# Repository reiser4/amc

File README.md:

# amc

Software utilizzato su Windows:

 Python 3.5.0
 https://www.python.org/ftp/python/3.5.0/python-3.5.0-amd64-webinstall.exe

 PyQt5 5.5
 http://sourceforge.net/projects/pyqt/files/PyQt5/PyQt-5.5/PyQt5-5.5-gpl-Py3.4-Qt5.5.0-x64.exe

 py2exe 0.9.2.0
 https://pypi.python.org/packages/any/p/py2exe/py2exe-0.9.2.0.win-amd64.exe#md5=05d90513c993b2f3ae0f7f21d69a6898

Per compilare per windows:

 python setup.py py2exe --includes sip

# funzionamento

il software AMC gira su beaglebone black. E` costituito da diversi componenti che interagiscono tra loro solamente tramite lettura e scrittura (atomica) di files in /tmp.

/tmp/band.txt
	contiene la banda in uso. puo` essere: 160, 80, 60, 40, 30, 20, 17, 15, 12, 10, 6

/tmp/relay.txt
	descrive i rele` attivi con la combinazione attuale di preset.
	esempio: 100000000000000000000000
	nella nostra implementazione usiamo i primi otto bits

/tmp/presetA.txt e /tmp/presetB.txt
	descrivono la combinazione da tastiera scelta dall'utente
	la pressione dei tasti provoca la variazione della combinazione
	esempio:
		TX: 01100000
		RX: 10010000

/tmp/presetTXTA.txt e /tmp/presetTXTB.txt
	contiene la lista testuale di preset attivi (per essere stampato sul display)
	senza spazi, separati da virgola, poi punto e virgola tra Rx e Tx
	esempio:
		Europa,Asia,America;Asia

/tmp/tx.txt
	contiene la lista di radio che stanno trasmettendo in quel momento
	esempio:
		A
		oppure
		B
		oppure 
		(file vuoto)

/root/amc/config.json
	contiene la configurazione con cui vengono determinate le varie combinazioni di relay da accendere.
	vedi file di esempio

# componenti software

MAIN:
	si occupa di prendere le decisioni riguardo i preset e relay da attivare.
	LEGGE: /root/amc/config.json /tmp/tx.txt /tmp/presetA.txt /tmp/presetB.txt /tmp/band.txt
	SCRIVE: /tmp/relay.txt /tmp/presetTXTA.txt /tmp/presetTXTB.txt

IOLOOP:
	ascolta il GPIO hardware per determinare la banda e la radio trasmittente.
	SCRIVE: /tmp/band.txt /tmp/tx.txt

DISPLAY:
	si occupa di mantenere il display aggiornato con lo stato attuale.
	LEGGE: /tmp/tx.txt /tmp/band.txt /tmp/presetTXTA.txt /tmp/presetTXTB.txt

KEYBOARD:
	rimane in ascolto di input da tastiera e fa i toggle dei bits dei preset
	LEGGE: /tmp/presetA.txt /tmp/presetB.txt
	SCRIVE: /tmp/presetA.txt /tmp/presetB.txt

SERIAL:
	svolge due funzioni: riporta periodicamente sulla seriale lo stato attuale per poter essere visualizzato sul pc,
	ed interagisce col pc per inviare e ricevere la configurazione.
	LEGGE: /tmp/presetA.txt /tmp/presetB.txt /tmp/tx.txt /tmp/band.txt /tmp/presetTXTA.txt /tmp/presetTXTB.txt /root/amc/config.json
	SCRIVE: /root/amc/config.json

RELAY:
	scrive su GPIO le uscite relay
	LEGGE: /tmp/relay.txt

CHECK:
	verifica che tutti i processi siano in esecuzione ed avvia eventuali processi fermi.

===================================

Requisiti software

# apt-get install git
# pip install Pillow

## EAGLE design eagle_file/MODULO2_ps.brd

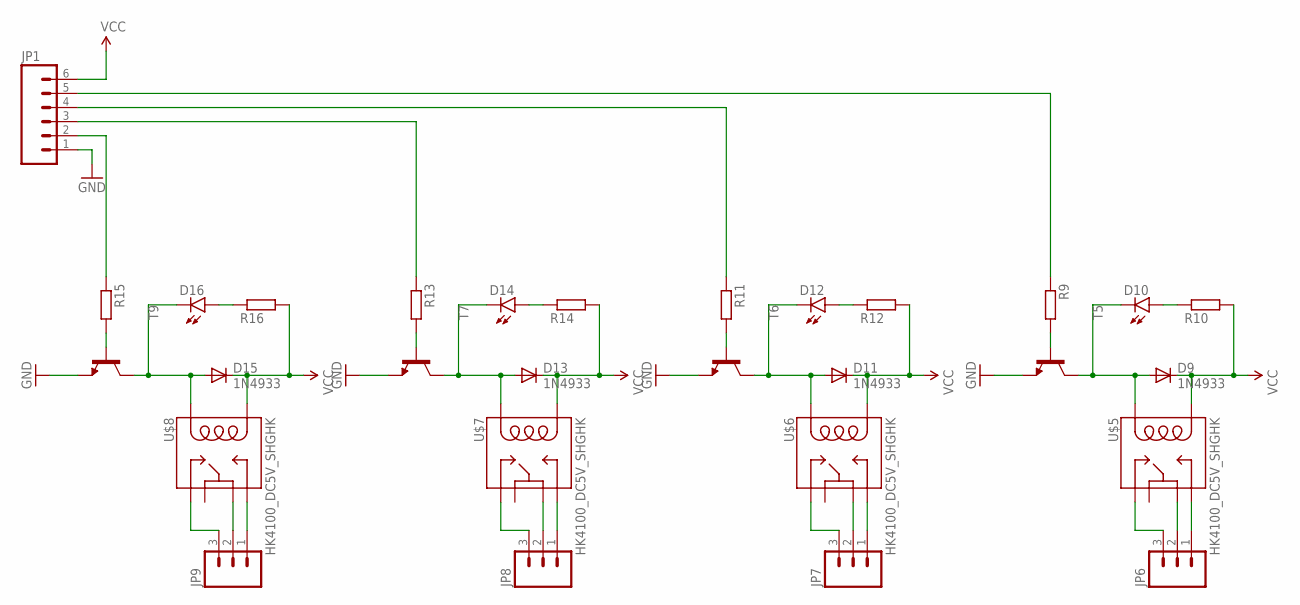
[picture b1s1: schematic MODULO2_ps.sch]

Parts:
D9, D11, D13, D15: 1N4933; DO41-10
D10, D12, D14, D16: LED5MM
JP1: M06SILK_FEMALE_PTH; 1X06
JP6, JP7, JP8, JP9: M03-SCREW-5MM; SCREWTERMINAL-5MM-3
R9, R10, R11, R12, R13, R14, R15, R16: R-EU_R0805; R0805
T5, T6, T7, T9: -NPN-TO92-EBC; TO92-EBC
U$5, U$6, U$7, U$8: HK4100_DC5V_SHGHK; HK4100

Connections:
GND: JP1.1, T5.E, T6.E, T7.E, T9.E
unnamed: D9.A, D10.K (C), T5.C, U$5.6 (2)
unnamed: D10.A, R10.1
unnamed: R9.2, T5.B
unnamed: D11.A, D12.K (C), T6.C, U$6.6 (2)
unnamed: D12.A, R12.1
unnamed: R11.2, T6.B
unnamed: D13.A, D14.K (C), T7.C, U$7.6 (2)
unnamed: D14.A, R14.1
unnamed: R13.2, T7.B
unnamed: D15.A, D16.K (C), T9.C, U$8.6 (2)
unnamed: D16.A, R16.1
unnamed: R15.2, T9.B
unnamed: JP1.4, R11.1
unnamed: JP1.5, R9.1
unnamed: JP1.3, R13.1
unnamed: JP1.2, R15.1
unnamed: JP6.1, U$5.8 (10)
unnamed: JP6.2, U$5.14 (6)
unnamed: JP6.3, U$5.7 (1)
unnamed: JP7.1, U$6.8 (10)
unnamed: JP7.2, U$6.14 (6)
unnamed: JP7.3, U$6.7 (1)
unnamed: JP8.1, U$7.8 (10)
unnamed: JP8.2, U$7.14 (6)
unnamed: JP8.3, U$7.7 (1)
unnamed: JP9.1, U$8.8 (10)
unnamed: JP9.2, U$8.14 (6)
unnamed: JP9.3, U$8.7 (1)
VCC: D9.C, D11.C, D13.C, D15.C, JP1.6, R10.2, R12.2, R14.2, R16.2, U$5.9, U$6.9, U$7.9, U$8.9

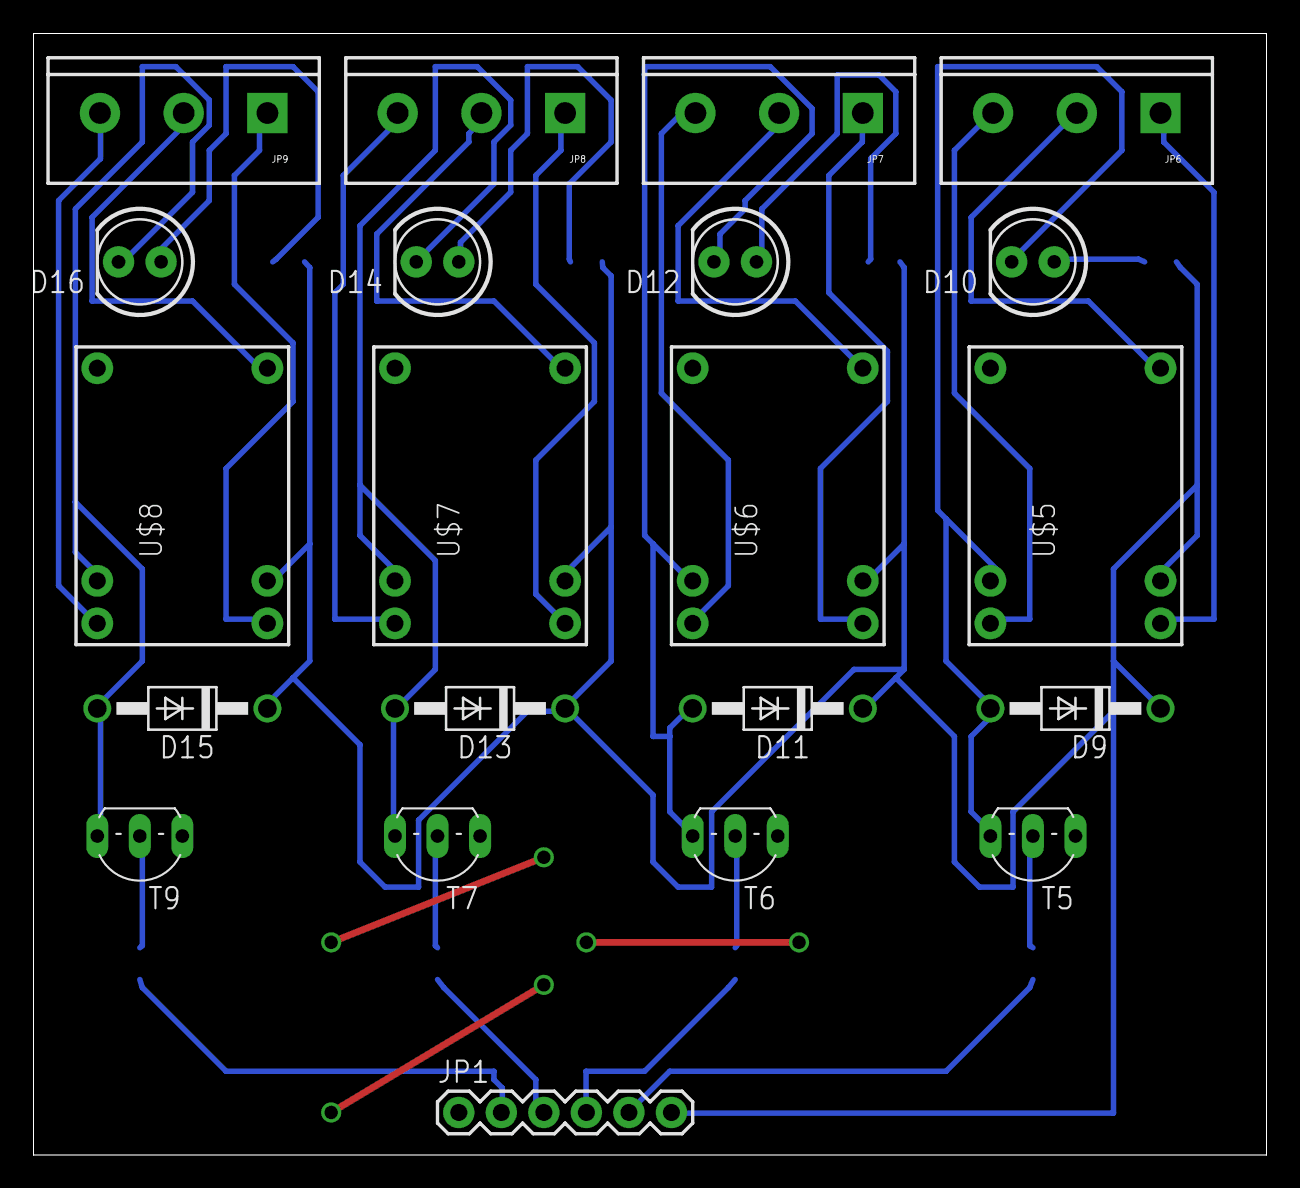
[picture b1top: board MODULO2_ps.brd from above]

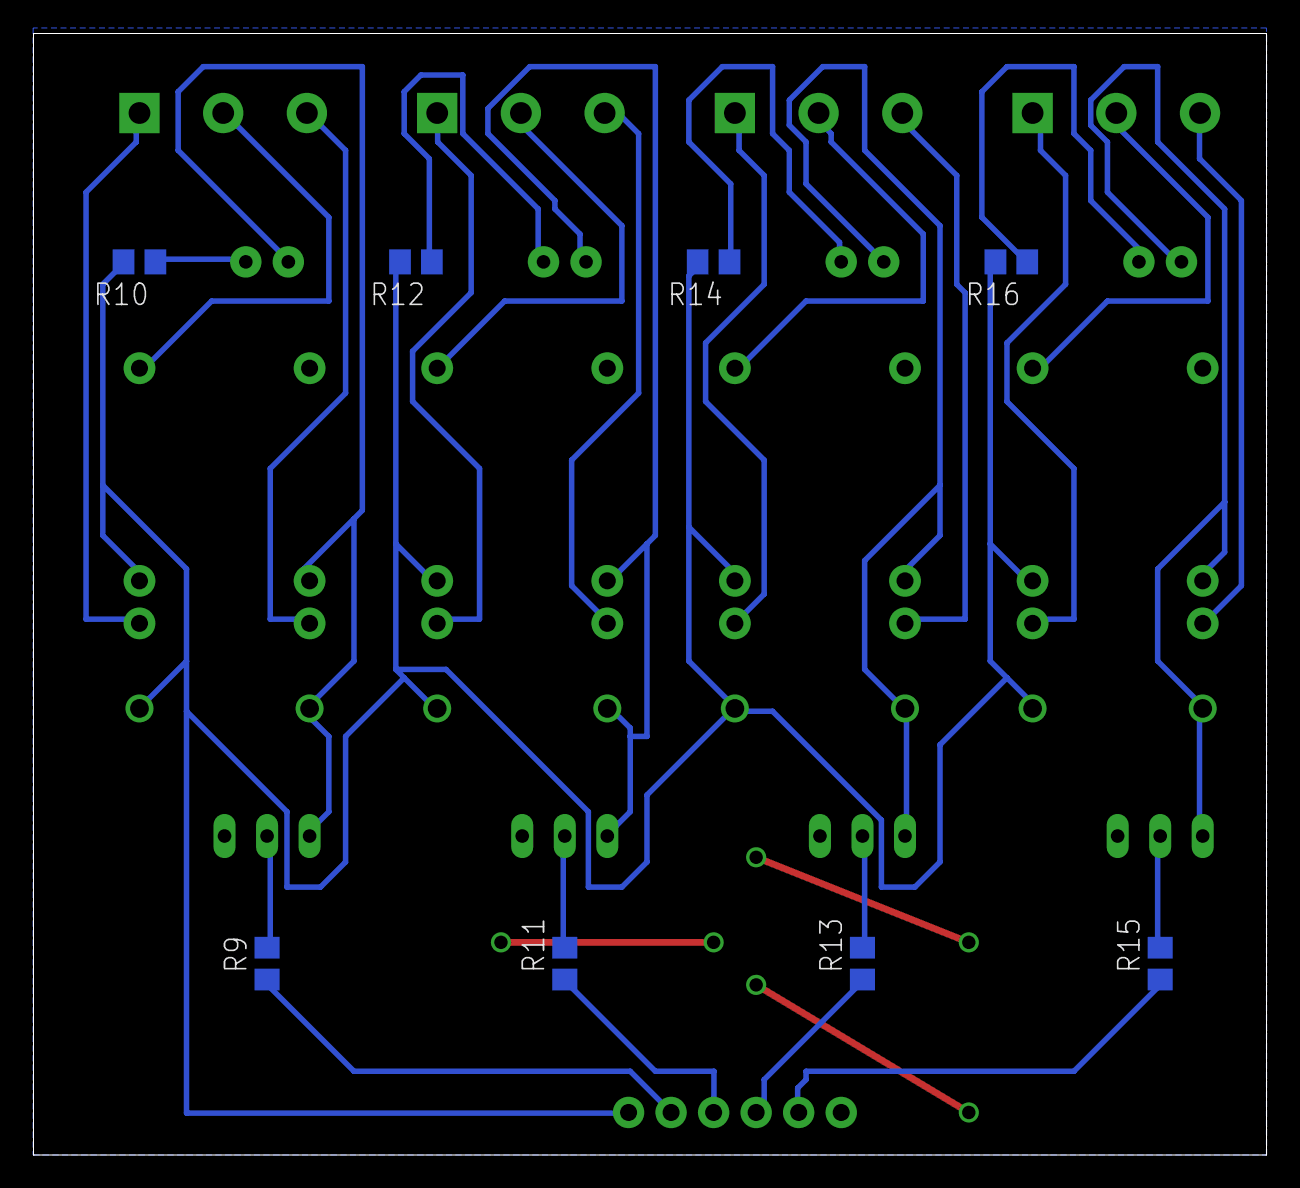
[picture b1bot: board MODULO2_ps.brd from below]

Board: 2 copper layers, 73.6 x 67.0 mm, 29 parts (8 on the bottom side), 30 nets.

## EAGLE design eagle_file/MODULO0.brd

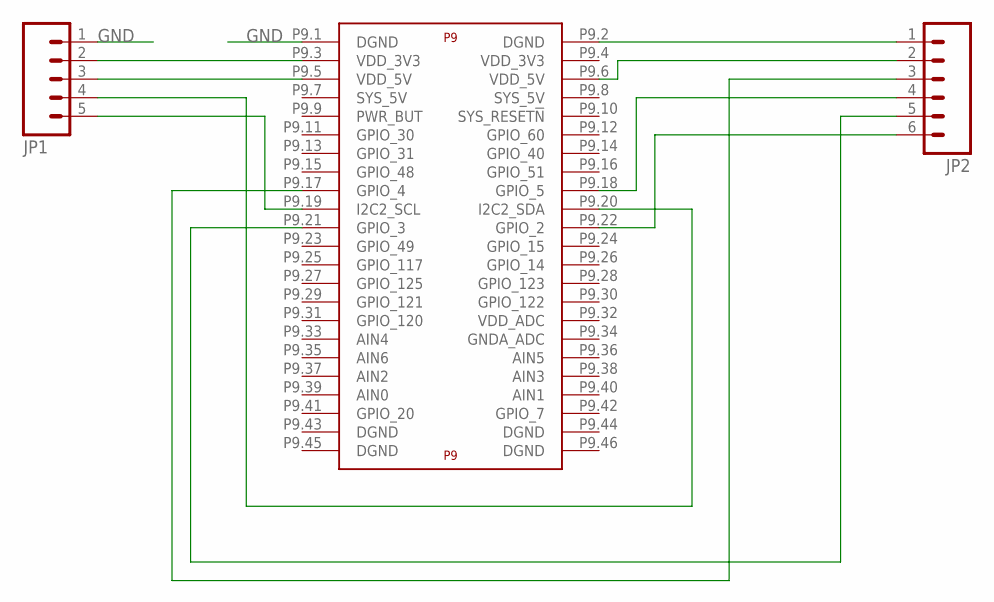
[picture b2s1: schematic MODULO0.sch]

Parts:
JP1: M05PTH; 1X05
JP2: M06SILK_FEMALE_PTH; 1X06
U$1: BEAGLE_BONE_BLACK_CAPE

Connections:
GND: JP1.1, U$1.P9.1 (DGND)
unnamed: JP1.2, U$1.P9.3 (VDD_3V3)
unnamed: JP1.3, U$1.P9.5 (VDD_5V)
unnamed: JP1.5, U$1.P9.19 (I2C2_SCL)
unnamed: JP1.4, U$1.P9.20 (I2C2_SDA)
unnamed: JP2.1, U$1.P9.2 (DGND)
unnamed: JP2.2, U$1.P9.6 (VDD_5V)
unnamed: JP2.3, U$1.P9.17 (GPIO_4)
unnamed: JP2.4, U$1.P9.18 (GPIO_5)
unnamed: JP2.6, U$1.P9.22 (GPIO_2)
unnamed: JP2.5, U$1.P9.21 (GPIO_3)

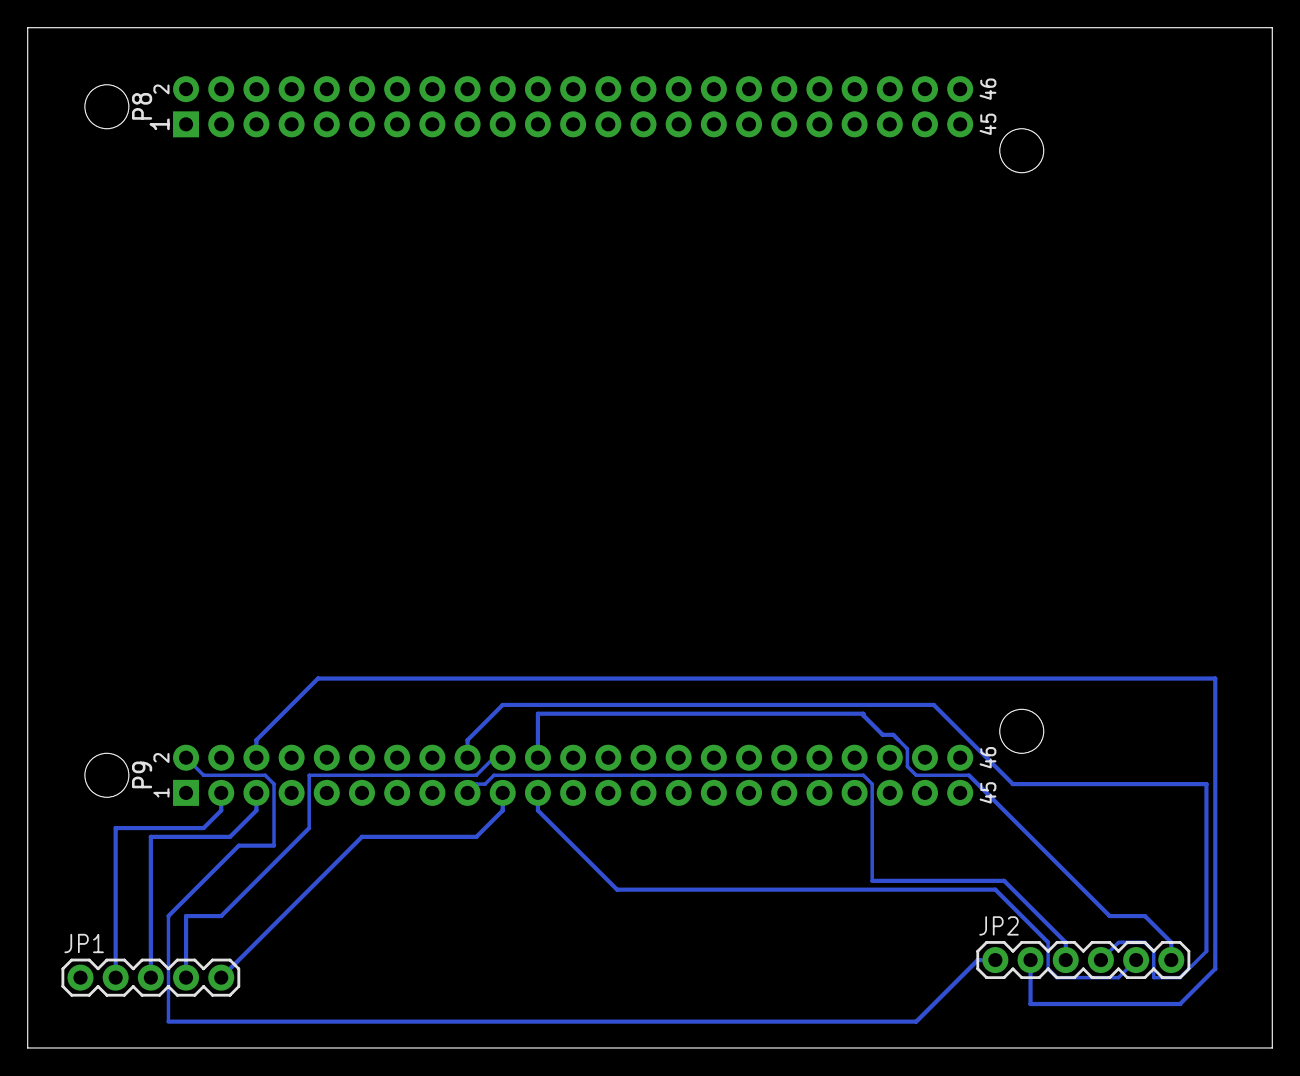
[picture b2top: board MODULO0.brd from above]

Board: 2 copper layers, 89.8 x 73.7 mm, 3 parts (0 on the bottom side), 11 nets.

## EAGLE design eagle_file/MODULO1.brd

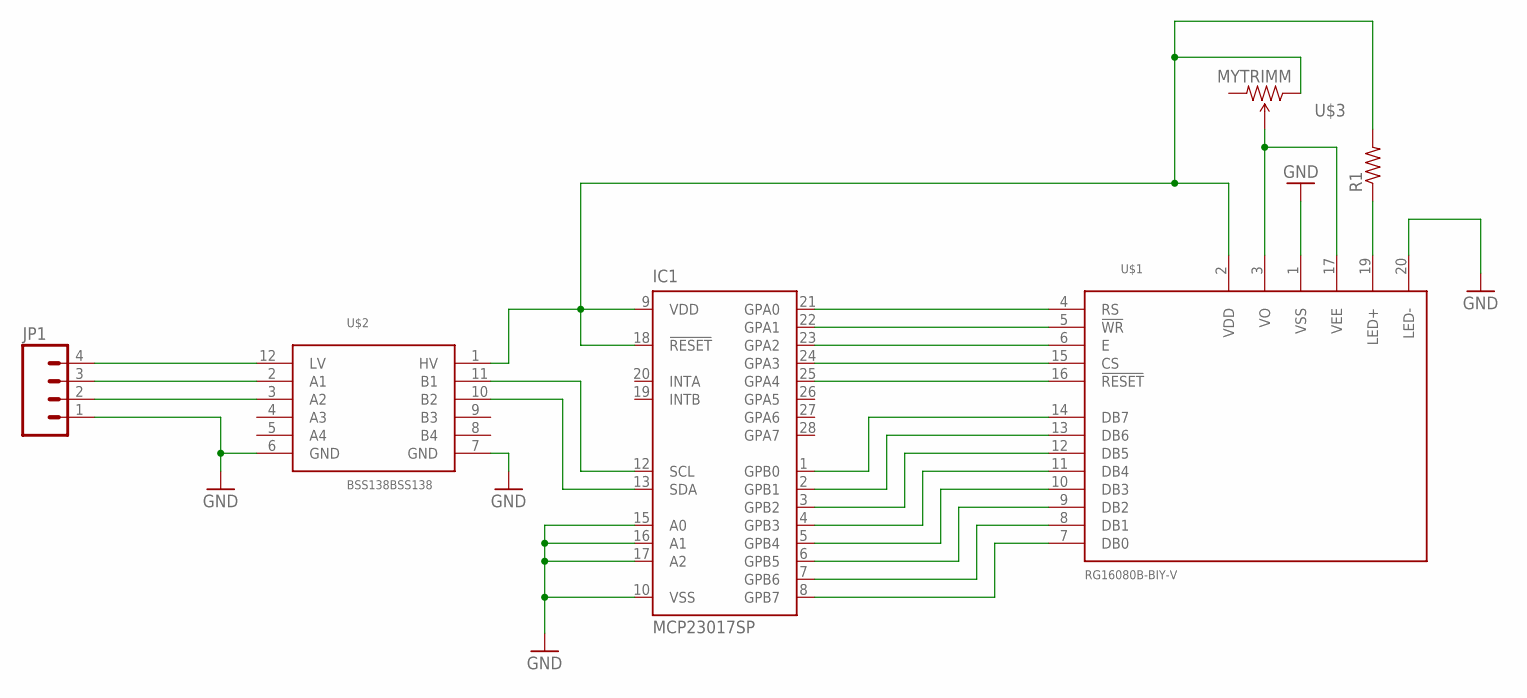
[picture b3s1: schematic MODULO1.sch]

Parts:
IC1: MCP23017SP; DIL28-3
JP1: M04PTH; 1X04
R1: RESISTOR0805-RES; 0805
U$1: RG16080B-BIY-V; 1X20
U$2: BSS138BSS138; BSS138
U$3: MYTRIMM

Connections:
GND: IC1.10 (VSS), IC1.15 (A0), IC1.16 (A1), IC1.17 (A2), JP1.1, U$1.1 (VSS), U$1.20 (LED-), U$2.6 (GND), U$2.7 (GND)
unnamed: IC1.21 (GPA0), U$1.4 (RS)
unnamed: IC1.22 (GPA1), U$1.5 (!WR)
unnamed: IC1.23 (GPA2), U$1.6 (E)
unnamed: IC1.24 (GPA3), U$1.15 (CS)
unnamed: IC1.25 (GPA4), U$1.16 (!RESET)
unnamed: IC1.1 (GPB0), U$1.14 (DB7)
unnamed: IC1.2 (GPB1), U$1.13 (DB6)
unnamed: IC1.3 (GPB2), U$1.12 (DB5)
unnamed: IC1.4 (GPB3), U$1.11 (DB4)
unnamed: IC1.5 (GPB4), U$1.10 (DB3)
unnamed: IC1.6 (GPB5), U$1.9 (DB2)
unnamed: IC1.7 (GPB6), U$1.8 (DB1)
unnamed: IC1.8 (GPB7), U$1.7 (DB0)
unnamed: IC1.9 (VDD), IC1.18 (!RESET), R1.2, U$1.2 (VDD), U$2.1 (HV), U$3.1 (CCW)
unnamed: IC1.12 (SCL), U$2.11 (B1)
unnamed: IC1.13 (SDA), U$2.10 (B2)
unnamed: JP1.4, U$2.12 (LV)
unnamed: JP1.3, U$2.2 (A1)
unnamed: JP1.2, U$2.3 (A2)
unnamed: U$1.3 (VO), U$1.17 (VEE), U$3.2 (WIPER)
unnamed: R1.1, U$1.19 (LED+)

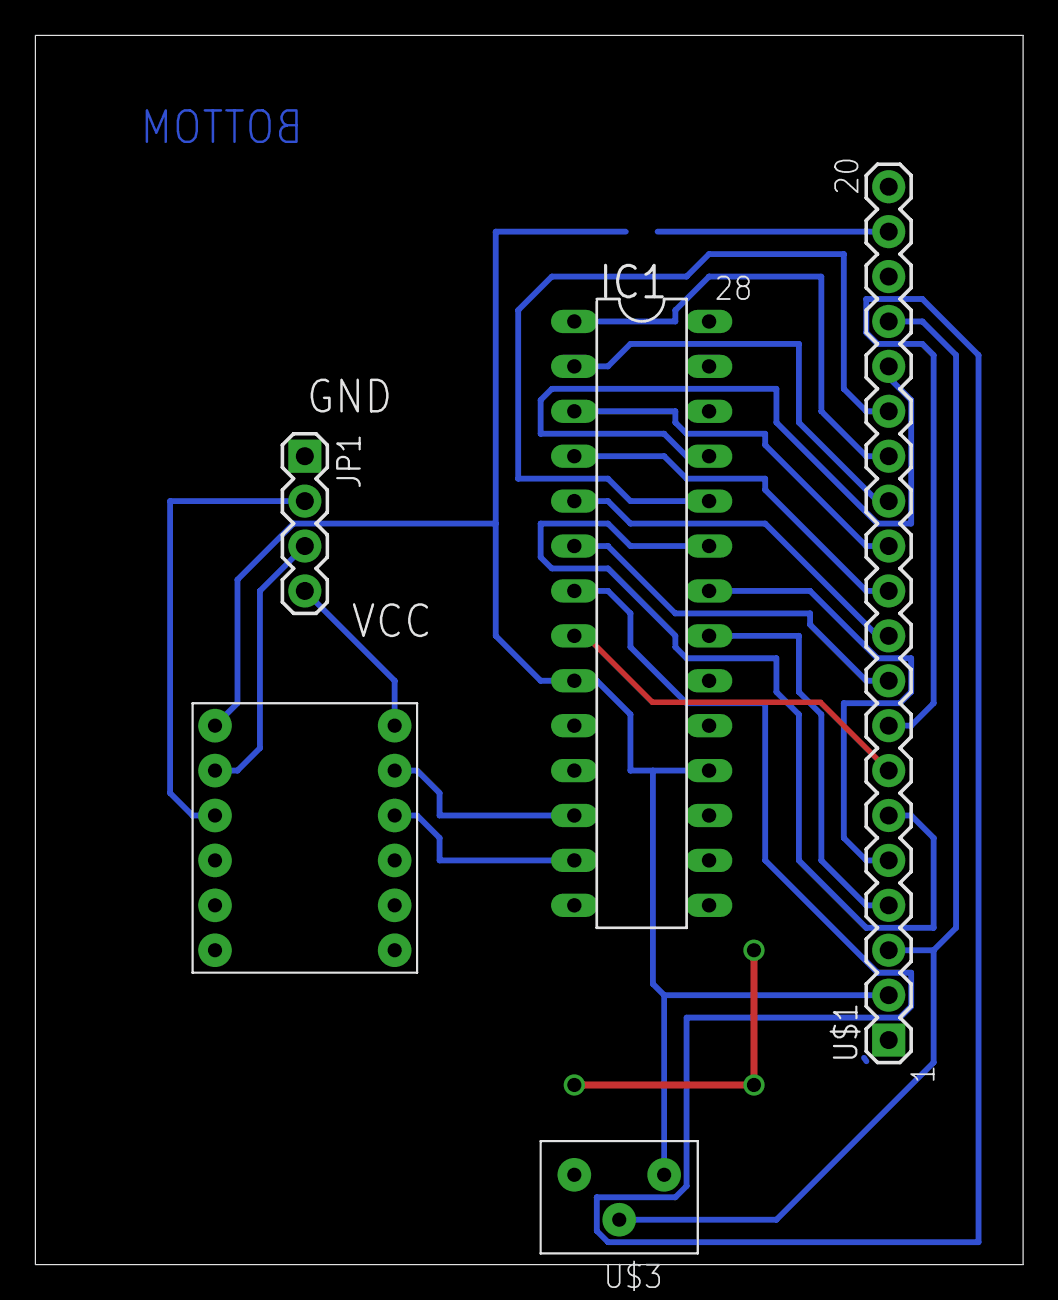
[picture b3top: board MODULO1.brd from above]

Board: 2 copper layers, 55.9 x 69.5 mm, 6 parts (1 on the bottom side), 22 nets.

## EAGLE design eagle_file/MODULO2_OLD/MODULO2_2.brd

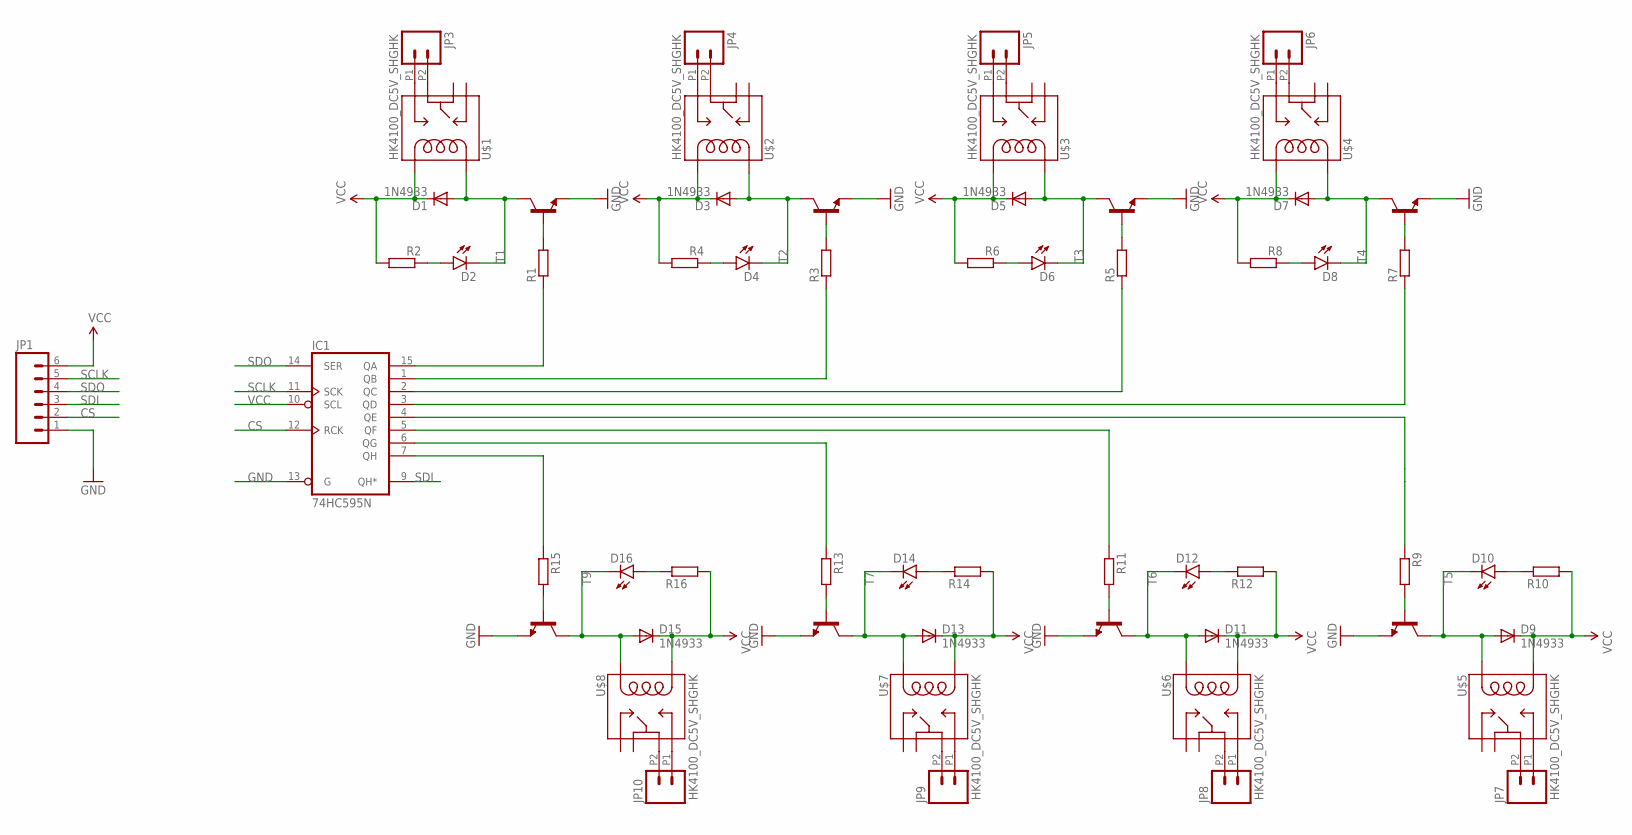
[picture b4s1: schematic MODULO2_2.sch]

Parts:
D1, D3, D5, D7, D9, D11, D13, D15: 1N4933; DO41-10
D2, D4, D6, D8, D10, D12, D14, D16: LED5MM
IC1: 74HC595N; DIL16
JP1: M06LOCK; 1X06_LOCK
JP3, JP4, JP5, JP6, JP7, JP8, JP9, JP10: M022.54MM_SCREWTERM; 1X02_2.54_SCREWTERM
R1, R2, R3, R4, R5, R6, R7, R8, R9, R10, R11, R12, R13, R14, R15, R16: R-EU_R0805; R0805
T1, T2, T3, T4, T5, T6, T7, T9: -NPN-TO92-EBC; TO92-EBC
U$1, U$2, U$3, U$4, U$5, U$6, U$7, U$8: HK4100_DC5V_SHGHK; HK4100

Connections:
CS: IC1.12 (RCK), JP1.2
GND: IC1.8 (GND), IC1.13 (G), JP1.1, T1.E, T2.E, T3.E, T4.E, T5.E, T6.E, T7.E, T9.E
unnamed: IC1.15 (QA), R1.1
unnamed: IC1.1 (QB), R3.1
unnamed: D1.A, D2.K (C), T1.C, U$1.6 (2)
unnamed: D2.A, R2.1
unnamed: R1.2, T1.B
unnamed: D3.A, D4.K (C), T2.C, U$2.6 (2)
unnamed: D5.A, D6.K (C), T3.C, U$3.6 (2)
unnamed: D6.A, R6.1
unnamed: R5.2, T3.B
unnamed: D7.A, D8.K (C), T4.C, U$4.6 (2)
unnamed: D8.A, R8.1
unnamed: R7.2, T4.B
unnamed: IC1.3 (QD), R7.1
unnamed: D4.A, R4.1
unnamed: R3.2, T2.B
unnamed: IC1.2 (QC), R5.1
unnamed: D9.A, D10.K (C), T5.C, U$5.6 (2)
unnamed: D10.A, R10.1
unnamed: R9.2, T5.B
unnamed: D11.A, D12.K (C), T6.C, U$6.6 (2)
unnamed: D12.A, R12.1
unnamed: R11.2, T6.B
unnamed: D13.A, D14.K (C), T7.C, U$7.6 (2)
unnamed: D14.A, R14.1
unnamed: R13.2, T7.B
unnamed: D15.A, D16.K (C), T9.C, U$8.6 (2)
unnamed: D16.A, R16.1
unnamed: R15.2, T9.B
unnamed: IC1.5 (QF), R11.1
unnamed: IC1.4 (QE), R9.1
unnamed: IC1.6 (QG), R13.1
unnamed: IC1.7 (QH), R15.1
unnamed: JP3.P1 (1), U$1.8 (10)
unnamed: JP3.P2 (2), U$1.14 (6)
unnamed: JP4.P1 (1), U$2.8 (10)
unnamed: JP4.P2 (2), U$2.14 (6)
unnamed: JP5.P1 (1), U$3.8 (10)
unnamed: JP5.P2 (2), U$3.14 (6)
unnamed: JP6.P1 (1), U$4.8 (10)
unnamed: JP6.P2 (2), U$4.14 (6)
unnamed: JP7.P1 (1), U$5.8 (10)
unnamed: JP7.P2 (2), U$5.14 (6)
unnamed: JP8.P1 (1), U$6.8 (10)
unnamed: JP8.P2 (2), U$6.14 (6)
unnamed: JP9.P1 (1), U$7.8 (10)
unnamed: JP9.P2 (2), U$7.14 (6)
unnamed: JP10.P1 (1), U$8.8 (10)
unnamed: JP10.P2 (2), U$8.14 (6)
SCLK: IC1.11 (SCK), JP1.5
SDI: IC1.9 (QH*), JP1.3
SDO: IC1.14 (SER), JP1.4
VCC: D1.C, D3.C, D5.C, D7.C, D9.C, D11.C, D13.C, D15.C, IC1.10 (SCL), IC1.16 (VCC), JP1.6, R2.2, R4.2, R6.2, R8.2, R10.2, R12.2, R14.2, R16.2, U$1.9, U$2.9, U$3.9, U$4.9, U$5.9, U$6.9, U$7.9, U$8.9

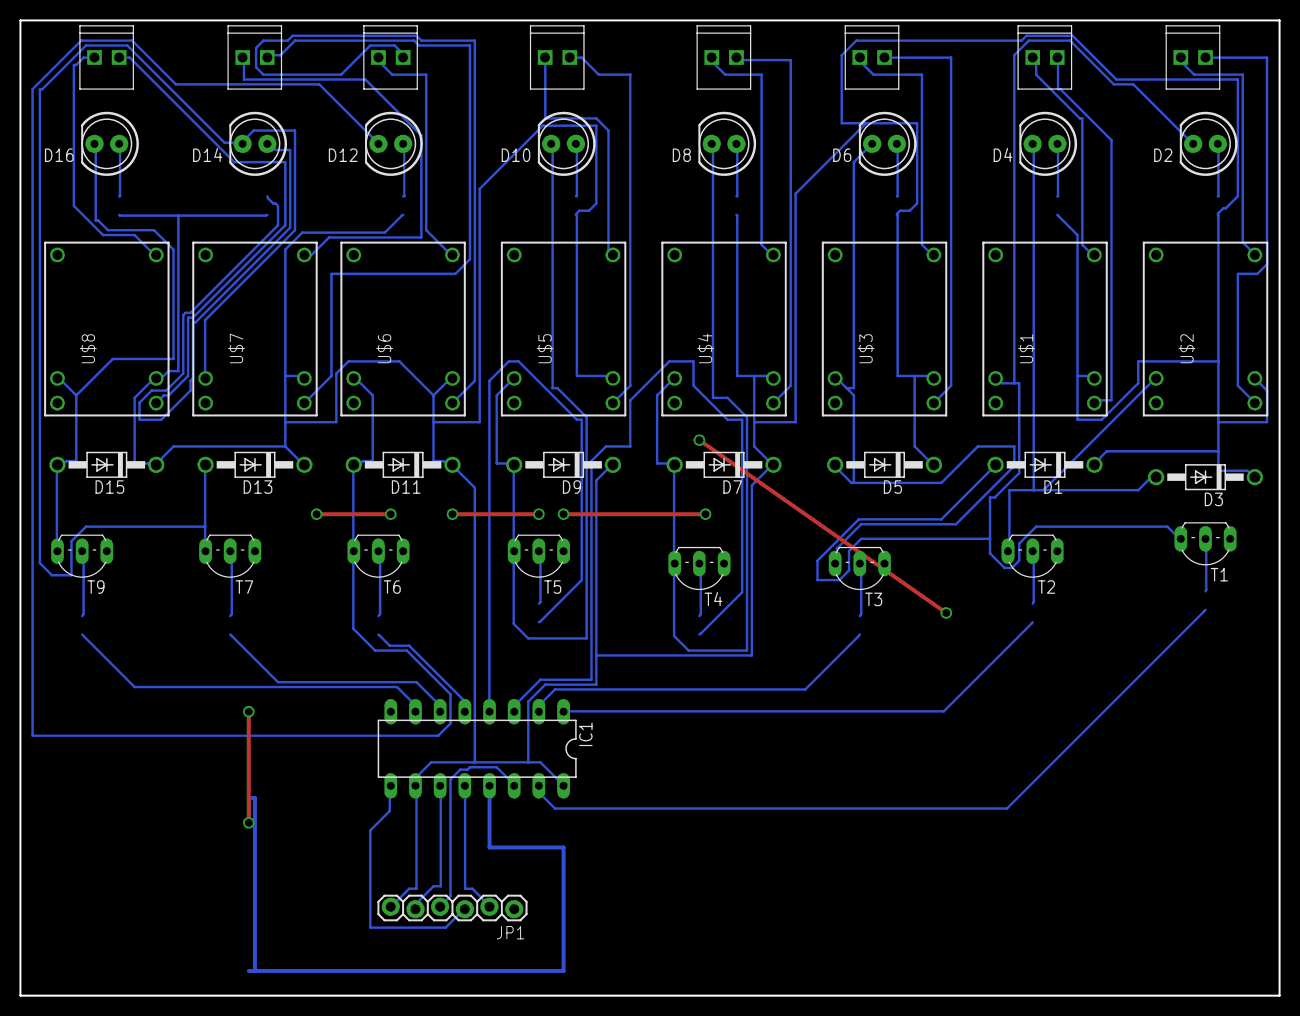
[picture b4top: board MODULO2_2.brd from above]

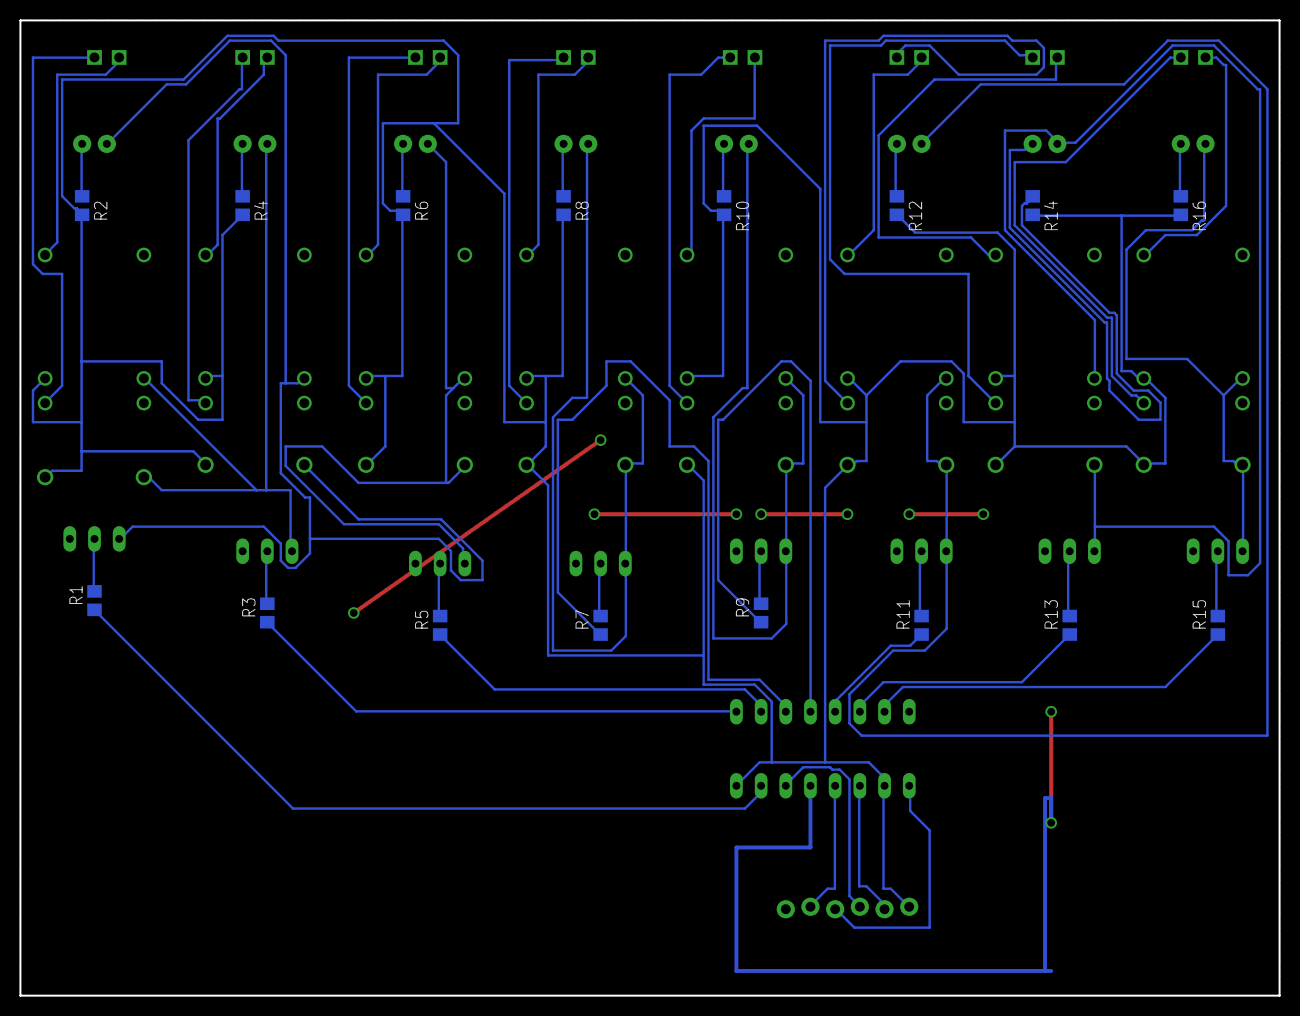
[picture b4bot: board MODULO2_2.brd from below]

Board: 2 copper layers, 129.5 x 100.3 mm, 58 parts (16 on the bottom side), 54 nets.

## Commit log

2015-04-14 commit iniziale
2015-04-14 rename
2015-04-14 test
2015-04-14 first-one-wins logic
2015-04-14 double = missing
2015-04-14 init and read radio ptt
2015-04-14 pin settings
2015-04-14 ptt logic
2015-04-14 debug
2015-04-20 configuration sample
2015-04-21 bcd picture
2015-04-21 web page
2015-04-21 prova
2015-04-21 web fix
2015-04-21 web page fix
2015-04-22 modifica read input xkeys
2015-04-22 front webpage
2015-04-22 aggiunti led sul frontale
2015-04-22 front simulator
2015-04-22 relay output
2015-04-24 relay visual output improved
2015-04-24 gitignore update
2015-04-24 creata classe per leggere da tastiera
2015-04-27 Schematic
2015-04-27 verbose text disabled; dxlog band decoder
2015-04-27 relay fix
2015-04-28 display beginning
2015-04-28 new class 'atomicwrite'
2015-04-29 keyboard as radio button, atomic front, cape
2015-04-29 add functions to writeRect and writeLine
2015-04-29 bug fix keyboardxkeys.py
2015-05-03 font and a few test
2015-05-07 Schema di base
2015-05-07 Collegato alla 5V
2015-05-18 display driver working
2015-05-24 configuration panel test
2015-05-24 ricarico il file dxlog-band.py che nelle precedente commit ho cancellato
2015-05-26 aggiunta di commenti al file configuration-panel.py
2015-05-28 Schematico Logico
2015-06-01 Revert "Merge branch 'master' of https://github.com/reiser4/amc"
    This reverts commit 2380cc5f35dc9174c4fa96b8073f98d69a9940f7, reversing
    changes made to 8732c452cd3d8e44b63f819e5c39efa00f12953a.
2015-06-01 Revert "Revert "Merge branch 'master' of https://github.com/reiser4/amc""
    This reverts commit 9bf984cd97639c6bb09fb1a1b6d99ebaa172ac6a.
2015-06-01 Fix typos and default settings and state
2015-06-01 Working on printing text on display
2015-06-02 configuration panel row and column decode
2015-06-20 now configuration-panel.py can save configuration
2015-06-20 fix bug for save configuration
2015-06-21 now configuration-panel.py can load configuration
2015-06-21 add toolbar, icons for save and load configuration
2015-06-28 rinomino i file per seguire le linee guida di PEP8
2015-07-15 adesso possiamo decidere il nome del file da salvare
2015-07-23 status to serial port
2015-07-23 got display
2015-07-23 work on display
2015-07-23 display cycle sleep
2015-07-29 Eagle File
    Schematics made in Eagle
2015-07-29 GND to MODULO0
    Ho messo a massa il Modulo0
2015-07-29 Modulo0 pdf
    Come da titolo
2015-07-29 Modulo 0 pdf
    Modulo 0 senza contorno ai fori
2015-07-29 Fix Modulo 0
    Pin all'esterno della scheda
2015-07-30 Modulo 2_2 pdf
2015-07-30 Modulo 2_1
    Modolo2_1.pdf per controllare i footprint
2015-07-30 MODULO2_def
2015-07-30 PDF Vari
    Ecco Tutti i pdf
2015-07-31 Fix PDF
    Ho tolto alcuni layer inutili dal pdf dei PCB
2015-08-05 viewpanel.py alpha
2015-08-07 viewpanel.py beta
2015-08-07 aggiunta la possibilità di fare l'upload della configurazione sul beaglebone in configpanel.py
2015-08-08 use os.path for the icons
2015-09-03 Divisione di modulo 2
2015-09-04 pdf MODULO2
2015-09-08 gerbers
2015-09-08 MODULO2_OLD
2015-09-10 Modulo1
2015-09-10 Modulo1 greber
2015-09-10 Modulo0
2015-09-11 Modulo2
2015-09-29 exe standalone
2015-09-29 readme
2015-10-15 Modulo ShiftRegister
    Aggiunto il modulo ShiftRegister, scritto con pseudocodice.
2015-10-16 shift register working
2015-10-26 new readme. shiftregister
2015-10-26 riorganizzazione file
2015-10-26 moved shiftregister
2015-10-26 relay now working
2015-10-26 relay complete
2015-10-26 relay is now foolproof
2015-10-26 display almost finished and almost foolproof
2015-10-26 keyboard OK for 1 keyboard
2015-10-26 display shows preset A
2015-10-27 moved files around
2015-10-27 python2 to python3...
2015-10-27 view panel working
2015-10-29 display driver in C
2015-11-01 corretti alcuni errori del viewpanel
2015-11-01 corretti alcuni errori nel configpanel
2015-11-03 run script
2015-11-03 serial renamed
2015-11-03 cosmetics
2015-11-04 serial upload working
2015-11-06 aggiunta possibilità di download e upload configurazione nel configpanel
2015-11-06 upload working
2015-11-06 download working
2015-11-06 current conf. upload almost working
2015-11-06 saving config only before upload
2015-11-06 fix per spazi
2016-06-21 prima di reindent
2016-08-05 requisiti
2016-08-15 lavori su main per versione finale
2016-08-15 relay ok!!!!!
2017-08-07 letta banda da piedini giusti; scrittura display su file; fix tastiere

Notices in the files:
parts and their libraries:
SparkFun-Connectors: Licensing: Creative Commons ShareAlike 4.0 International - https://creativecommons.org/licenses/by-sa/4.0
